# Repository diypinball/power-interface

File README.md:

# power-interface
Power Interace board for DIYPinball. Allows easy connection of screw terminal power supplies to the DIYPinball connector.

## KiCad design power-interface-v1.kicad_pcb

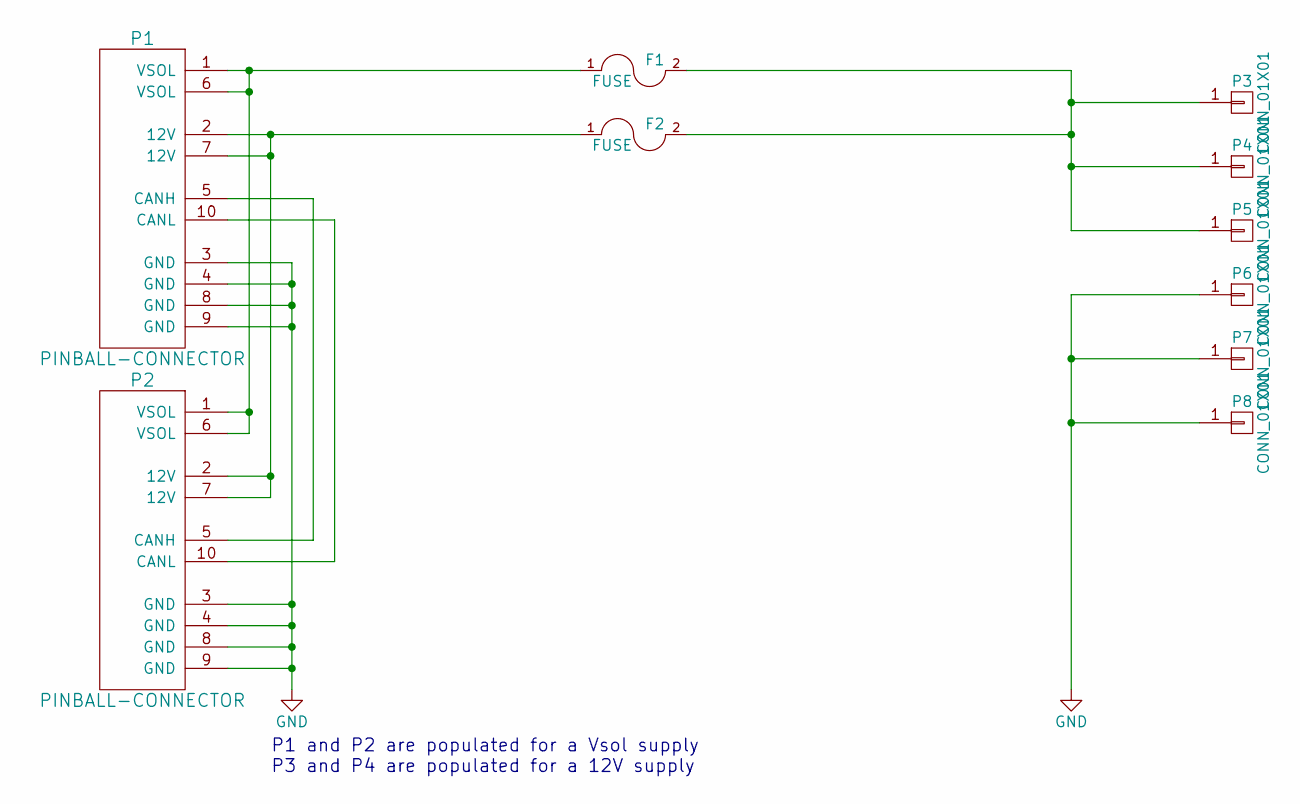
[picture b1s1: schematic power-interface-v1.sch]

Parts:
F1, F2: FUSE; FC203-20MM
P1, P2: PINBALL-CONNECTOR; PINBALL-CONNECTOR-V
P3, P4, P5, P6, P7, P8: CONN_01X01; PSU-HOLE

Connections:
GND: P1.3 (GND), P1.4 (GND), P1.8 (GND), P1.9 (GND), P2.3 (GND), P2.4 (GND), P2.8 (GND), P2.9 (GND), P6.1, P7.1, P8.1
unnamed: F1.1, P1.1 (VSOL), P1.6 (VSOL), P2.1 (VSOL), P2.6 (VSOL)
unnamed: F1.2, F2.2, P3.1, P4.1, P5.1
unnamed: F2.1, P1.2 (12V), P1.7 (12V), P2.2 (12V), P2.7 (12V)
unnamed: P1.5 (CANH), P2.5 (CANH)
unnamed: P1.10 (CANL), P2.10 (CANL)

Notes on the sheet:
P1 and P2 are populated for a Vsol supply P3 and P4 are populated for a 12V supply

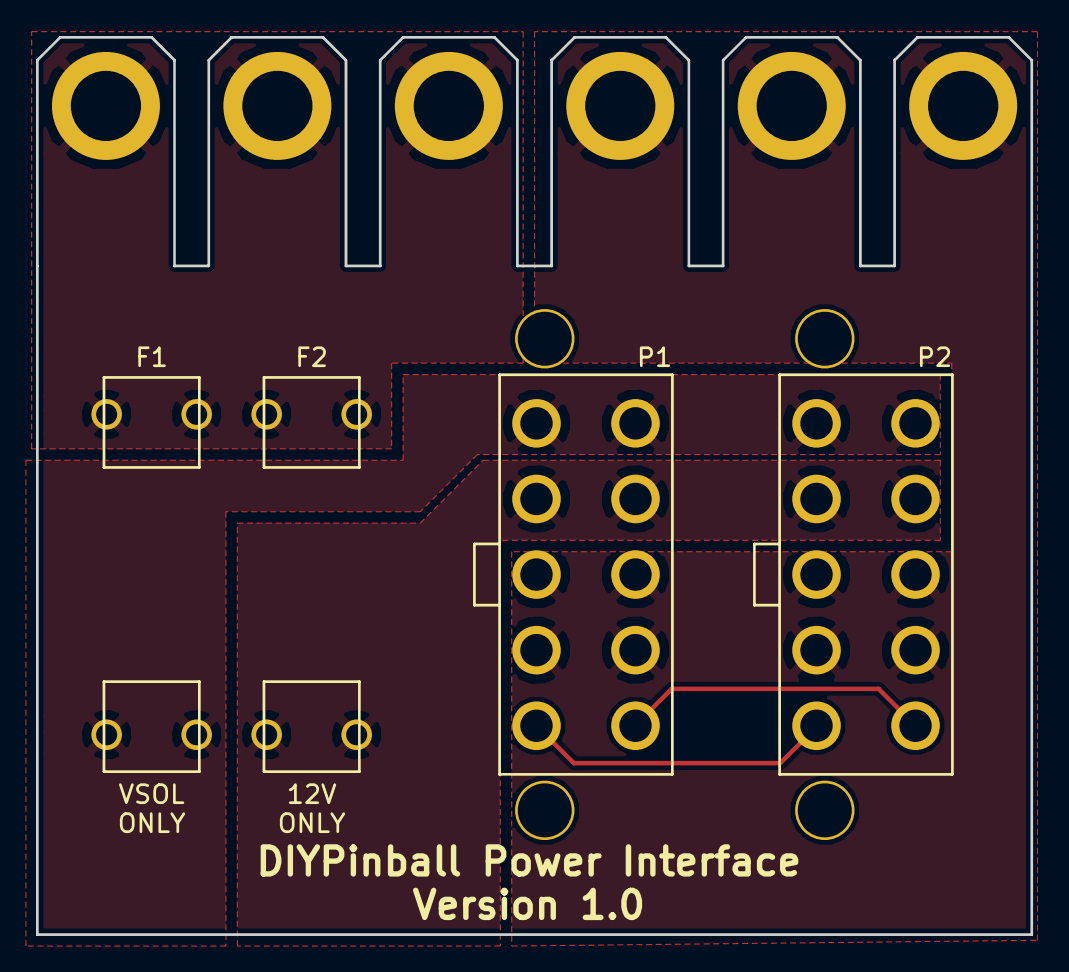
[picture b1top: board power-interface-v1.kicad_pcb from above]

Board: 2 copper layers, 55.2 x 49.8 mm, 10 parts (0 on the bottom side), 6 nets.

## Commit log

2015-10-15 Adding power interface board, first revision
2015-10-16 Updating power interface to use fuses, and to use them to choose between a 12V and Vsol supply
